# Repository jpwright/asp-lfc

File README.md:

asp-lfc
=======

Schematics and code for my MEng project, a portable light field camera based on angle-sensitive pixel imager.

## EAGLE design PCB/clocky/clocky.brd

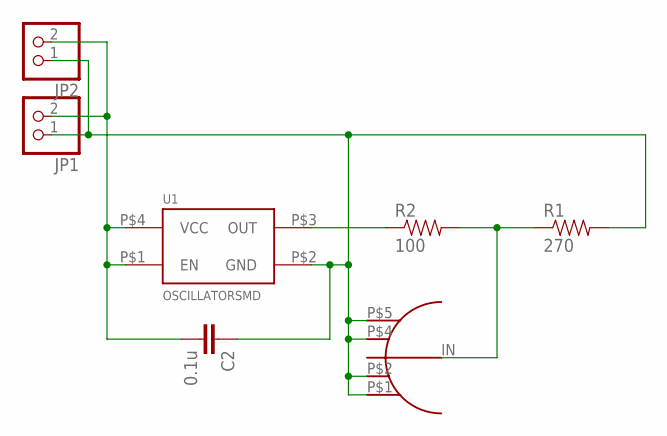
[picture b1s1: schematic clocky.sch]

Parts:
C2: 0.1u; 0603-CAP
JP1: PINHD-1X2/90; 1X02/90
JP2: PINHD-1X2; 1X02
R1: 270; 0603-RES
R2: 100; 0603-RES
U1: OSCILLATORSMD; CRYSTAL-SMD-7X5
U$1: J658; SMA_J658

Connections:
3V3: C2.2, JP1.2, JP2.2, U1.P$1 (EN), U1.P$4 (VCC)
GND: C2.1, JP1.1, JP2.1, R1.2, U1.P$2 (GND), U$1.P$1 (GNDA), U$1.P$2 (GNDB), U$1.P$4 (GNDC), U$1.P$5 (GNDD)
unnamed: R2.1, U1.P$3 (OUT)
unnamed: R1.1, R2.2, U$1.IN

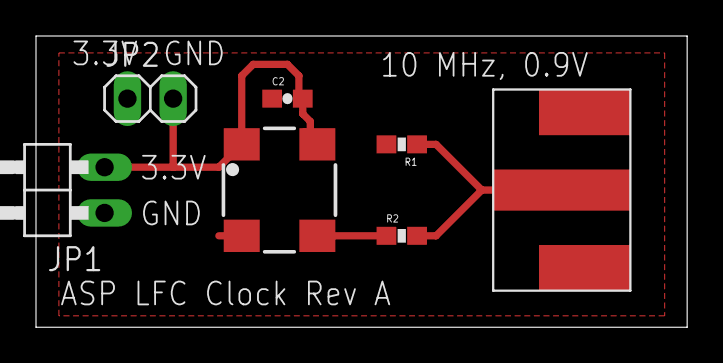
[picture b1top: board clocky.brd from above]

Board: 2 copper layers, 36.2 x 16.2 mm, 7 parts (0 on the bottom side), 4 nets.

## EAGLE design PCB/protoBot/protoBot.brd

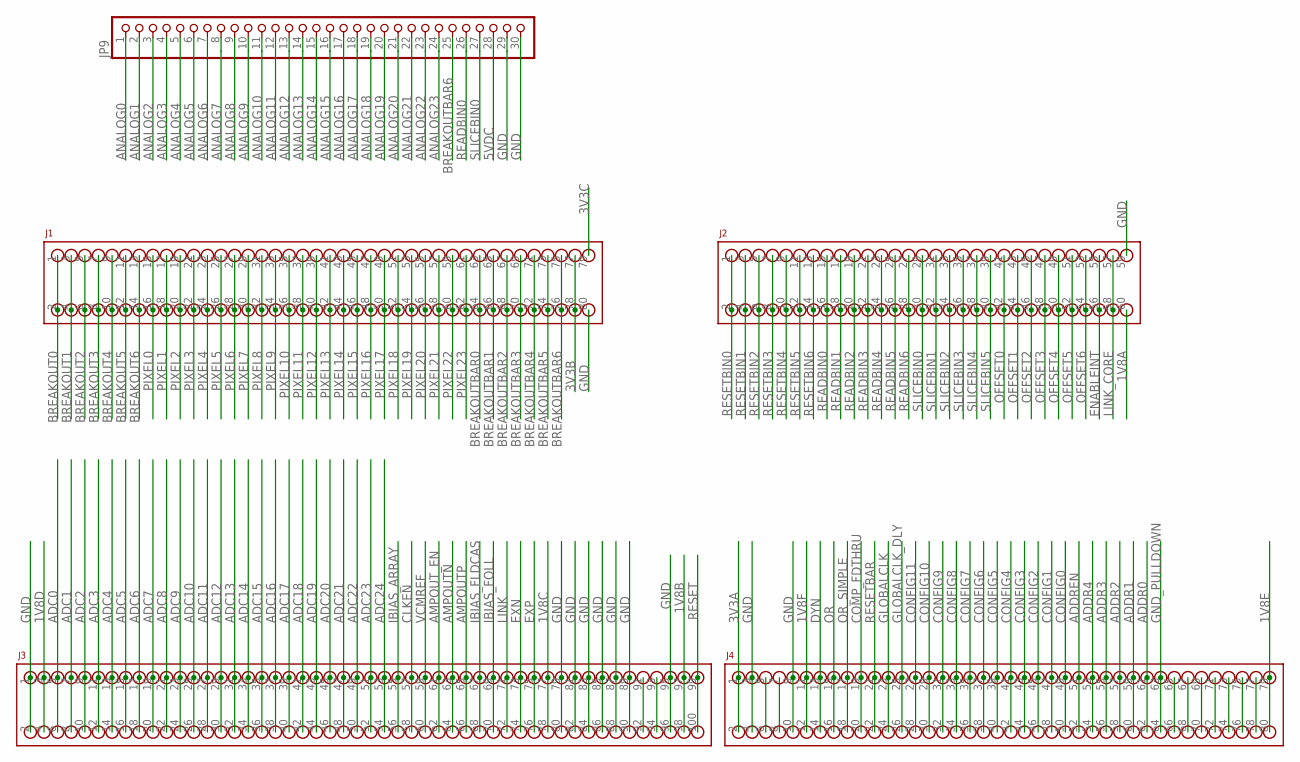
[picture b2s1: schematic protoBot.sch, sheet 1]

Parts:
J1, J4: AMPMODU50-80
J2: AMPMODU50-60
J3: AMPMODU50-100
JP9: PINHD-1X30; 1X30

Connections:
1V8A: J2.60; also elsewhere on the board
1V8B: J3.97, J3.98; also elsewhere on the board
1V8C: J3.77, J3.78; also elsewhere on the board
1V8D: J3.3, J3.4; also elsewhere on the board
1V8E: J4.79, J4.80; also elsewhere on the board
1V8F: J4.11, J4.12; also elsewhere on the board
3V3A: J4.1, J4.2; also elsewhere on the board
3V3B: J1.77, J1.78; also elsewhere on the board
3V3C: J1.79; also elsewhere on the board
5VDC: JP9.28; also elsewhere on the board
ADC0: J3.5, J3.6; also elsewhere on the board
ADC1: J3.7, J3.8; also elsewhere on the board
ADC2: J3.9, J3.10; also elsewhere on the board
ADC3: J3.11, J3.12; also elsewhere on the board
ADC4: J3.13, J3.14; also elsewhere on the board
ADC5: J3.15, J3.16; also elsewhere on the board
ADC6: J3.17, J3.18; also elsewhere on the board
ADC7: J3.19, J3.20; also elsewhere on the board
ADC8: J3.21, J3.22; also elsewhere on the board
ADC9: J3.23, J3.24; also elsewhere on the board
ADC10: J3.25, J3.26; also elsewhere on the board
ADC11: J3.27, J3.28; also elsewhere on the board
ADC12: J3.29, J3.30; also elsewhere on the board
ADC13: J3.31, J3.32; also elsewhere on the board
ADC14: J3.33, J3.34; also elsewhere on the board
ADC15: J3.35, J3.36; also elsewhere on the board
ADC16: J3.37, J3.38; also elsewhere on the board
ADC17: J3.39, J3.40; also elsewhere on the board
ADC18: J3.41, J3.42; also elsewhere on the board
ADC19: J3.43, J3.44; also elsewhere on the board
ADC20: J3.45, J3.46; also elsewhere on the board
ADC21: J3.47, J3.48; also elsewhere on the board
ADC22: J3.49, J3.50; also elsewhere on the board
ADC23: J3.51, J3.52; also elsewhere on the board
ADC24: J3.53, J3.54; also elsewhere on the board
ADDR0: J4.61, J4.62; also elsewhere on the board
ADDR1: J4.59, J4.60; also elsewhere on the board
ADDR2: J4.57, J4.58; also elsewhere on the board
ADDR3: J4.55, J4.56; also elsewhere on the board
ADDR4: J4.53, J4.54; also elsewhere on the board
ADDREN: J4.51, J4.52; also elsewhere on the board
AMPOUTN: J3.63, J3.64; also elsewhere on the board
AMPOUTP: J3.65, J3.66; also elsewhere on the board
AMPOUT_EN: J3.61, J3.62; also elsewhere on the board
ANALOG0: JP9.1; also elsewhere on the board
ANALOG1: JP9.2; also elsewhere on the board
ANALOG2: JP9.3; also elsewhere on the board
ANALOG3: JP9.4; also elsewhere on the board
ANALOG4: JP9.5; also elsewhere on the board
ANALOG5: JP9.6; also elsewhere on the board
ANALOG6: JP9.7; also elsewhere on the board
ANALOG7: JP9.8; also elsewhere on the board
ANALOG8: JP9.9; also elsewhere on the board
ANALOG9: JP9.10; also elsewhere on the board
ANALOG10: JP9.11; also elsewhere on the board
ANALOG11: JP9.12; also elsewhere on the board
ANALOG12: JP9.13; also elsewhere on the board
ANALOG13: JP9.14; also elsewhere on the board
ANALOG14: JP9.15; also elsewhere on the board
ANALOG15: JP9.16; also elsewhere on the board
ANALOG16: JP9.17; also elsewhere on the board
ANALOG17: JP9.18; also elsewhere on the board
ANALOG18: JP9.19; also elsewhere on the board
ANALOG19: JP9.20; also elsewhere on the board
ANALOG20: JP9.21; also elsewhere on the board
ANALOG21: JP9.22; also elsewhere on the board
ANALOG22: JP9.23; also elsewhere on the board
ANALOG23: JP9.24; also elsewhere on the board
BREAKOUT0: J1.1, J1.2; also elsewhere on the board
BREAKOUT1: J1.3, J1.4; also elsewhere on the board
BREAKOUT2: J1.5, J1.6; also elsewhere on the board
BREAKOUT3: J1.7, J1.8; also elsewhere on the board
BREAKOUT4: J1.9, J1.10; also elsewhere on the board
BREAKOUT5: J1.11, J1.12; also elsewhere on the board
BREAKOUT6: J1.13, J1.14; also elsewhere on the board
BREAKOUTBAR0: J1.63, J1.64; also elsewhere on the board
BREAKOUTBAR1: J1.65, J1.66; also elsewhere on the board
BREAKOUTBAR2: J1.67, J1.68; also elsewhere on the board
BREAKOUTBAR3: J1.69, J1.70; also elsewhere on the board
BREAKOUTBAR4: J1.71, J1.72; also elsewhere on the board
BREAKOUTBAR5: J1.73, J1.74; also elsewhere on the board
BREAKOUTBAR6: J1.75, J1.76, JP9.25; also elsewhere on the board
CLKEN: J3.57, J3.58; also elsewhere on the board
COMP_FDTHRU: J4.19, J4.20; also elsewhere on the board
CONFIG0: J4.49, J4.50; also elsewhere on the board
CONFIG1: J4.47, J4.48; also elsewhere on the board
CONFIG2: J4.45, J4.46; also elsewhere on the board
CONFIG3: J4.43, J4.44; also elsewhere on the board
CONFIG4: J4.41, J4.42; also elsewhere on the board
CONFIG5: J4.39, J4.40; also elsewhere on the board
CONFIG6: J4.37, J4.38; also elsewhere on the board
CONFIG7: J4.35, J4.36; also elsewhere on the board
CONFIG8: J4.33, J4.34; also elsewhere on the board
CONFIG9: J4.31, J4.32; also elsewhere on the board
CONFIG10: J4.29, J4.30; also elsewhere on the board
CONFIG11: J4.27, J4.28; also elsewhere on the board
DYN: J4.13, J4.14
ENABLEINT: J2.55, J2.56; also elsewhere on the board
EXN: J3.73, J3.74; also elsewhere on the board
EXP: J3.75, J3.76; also elsewhere on the board
GLOBALCLK: J4.23, J4.24
GLOBALCLK_DLY: J4.25, J4.26
GND: J1.80, J2.59, J3.1, J3.2, J3.79, J3.80, J3.81, J3.82, J3.83, J3.84, J3.85, J3.86, J3.87, J3.88, J3.89, J3.90, J3.95, J3.96, J4.3, J4.4, J4.9, J4.10, JP9.29, JP9.30; also elsewhere on the board
GND_PULLDOWN: J4.63, J4.64; also elsewhere on the board
IBIAS_ARRAY: J3.55, J3.56; also elsewhere on the board
IBIAS_FLDCAS: J3.67, J3.68; also elsewhere on the board
IBIAS_FOLL: J3.69, J3.70; also elsewhere on the board
LINK: J3.71, J3.72; also elsewhere on the board
LINK_CORE: J2.57, J2.58; also elsewhere on the board
unnamed: J4.5, J4.6
unnamed: J4.7, J4.8
unnamed: J4.65, J4.66
unnamed: J4.67, J4.68
unnamed: J4.69, J4.70
unnamed: J4.71, J4.72
unnamed: J4.73, J4.74
unnamed: J4.75, J4.76
unnamed: J4.77, J4.78
unnamed: J3.91, J3.92
unnamed: J3.93, J3.94
OFFSET0: J2.41, J2.42; also elsewhere on the board
OFFSET1: J2.43, J2.44; also elsewhere on the board
OFFSET2: J2.45, J2.46; also elsewhere on the board
OFFSET3: J2.47, J2.48; also elsewhere on the board
OFFSET4: J2.49, J2.50; also elsewhere on the board
OFFSET5: J2.51, J2.52; also elsewhere on the board
OFFSET6: J2.53, J2.54; also elsewhere on the board
OR: J4.15, J4.16; also elsewhere on the board
OR_SIMPLE: J4.17, J4.18; also elsewhere on the board
PIXEL0: J1.15, J1.16; also elsewhere on the board
PIXEL1: J1.17, J1.18; also elsewhere on the board
PIXEL2: J1.19, J1.20; also elsewhere on the board
PIXEL3: J1.21, J1.22; also elsewhere on the board
PIXEL4: J1.23, J1.24; also elsewhere on the board
PIXEL5: J1.25, J1.26; also elsewhere on the board
PIXEL6: J1.27, J1.28; also elsewhere on the board
PIXEL7: J1.29, J1.30; also elsewhere on the board
PIXEL8: J1.31, J1.32; also elsewhere on the board
PIXEL9: J1.33, J1.34; also elsewhere on the board
PIXEL10: J1.35, J1.36; also elsewhere on the board
PIXEL11: J1.37, J1.38; also elsewhere on the board
PIXEL12: J1.39, J1.40; also elsewhere on the board
PIXEL13: J1.41, J1.42; also elsewhere on the board
PIXEL14: J1.43, J1.44; also elsewhere on the board
PIXEL15: J1.45, J1.46; also elsewhere on the board
PIXEL16: J1.47, J1.48; also elsewhere on the board
PIXEL17: J1.49, J1.50; also elsewhere on the board
PIXEL18: J1.51, J1.52; also elsewhere on the board
PIXEL19: J1.53, J1.54; also elsewhere on the board
PIXEL20: J1.55, J1.56; also elsewhere on the board
PIXEL21: J1.57, J1.58; also elsewhere on the board
PIXEL22: J1.59, J1.60; also elsewhere on the board
PIXEL23: J1.61, J1.62; also elsewhere on the board
READBIN0: J2.15, J2.16, JP9.26; also elsewhere on the board
READBIN1: J2.17, J2.18
READBIN2: J2.19, J2.20
READBIN3: J2.21, J2.22
READBIN4: J2.23, J2.24
READBIN5: J2.25, J2.26
READBIN6: J2.27, J2.28; also elsewhere on the board
RESET: J3.99, J3.100; also elsewhere on the board
RESETBAR: J4.21, J4.22
RESETBIN0: J2.1, J2.2
RESETBIN1: J2.3, J2.4
RESETBIN2: J2.5, J2.6
RESETBIN3: J2.7, J2.8
RESETBIN4: J2.9, J2.10
RESETBIN5: J2.11, J2.12
RESETBIN6: J2.13, J2.14
SLICEBIN0: J2.29, J2.30, JP9.27; also elsewhere on the board
SLICEBIN1: J2.31, J2.32; also elsewhere on the board
SLICEBIN2: J2.33, J2.34; also elsewhere on the board
SLICEBIN3: J2.35, J2.36; also elsewhere on the board
SLICEBIN4: J2.37, J2.38; also elsewhere on the board
SLICEBIN5: J2.39, J2.40; also elsewhere on the board
VCMREF: J3.59, J3.60; also elsewhere on the board

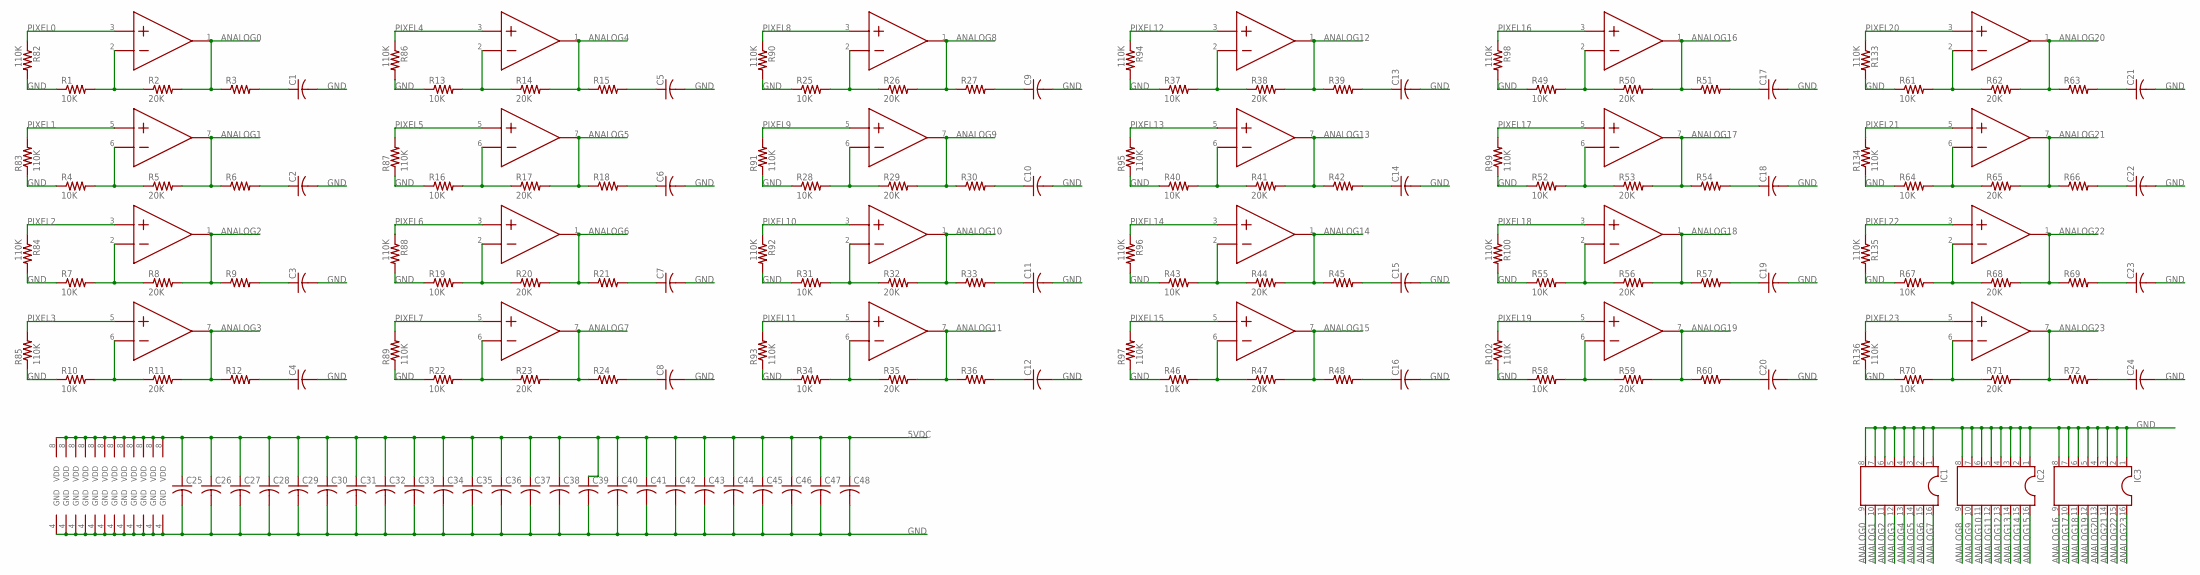
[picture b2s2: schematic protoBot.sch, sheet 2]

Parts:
C1, C2, C3, C4, C5, C6, C7, C8, C9, C10, C11, C12, C13, C14, C15, C16, C17, C18, C19, C20, C21, C22, C23, C24, C25, C26, C27, C28, C29, C30, C31, C32, C33, C34, C35, C36, C37, C38, C39, C40, C41, C42, C43, C44, C45, C46, C47, C48: C-USC0603; C0603
IC1, IC2, IC3: DIL16S; SOCKET-16
R1, R4, R7, R10, R13, R16, R19, R22, R25, R28, R31, R34, R37, R40, R43, R46, R49, R52, R55, R58, R61, R64, R67, R70: 10K; R0603
R2, R5, R8, R11, R14, R17, R20, R23, R26, R29, R32, R35, R38, R41, R44, R47, R50, R53, R56, R59, R62, R65, R68, R71: 20K; R0603
R3, R6, R9, R12, R15, R18, R21, R24, R27, R30, R33, R36, R39, R42, R45, R48, R51, R54, R57, R60, R63, R66, R69, R72: R-US_R0603; R0603
R82, R83, R84, R85, R86, R87, R88, R89, R90, R91, R92, R93, R94, R95, R96, R97, R98, R99, R100, R102, R133, R134, R135, R136: 110K; R0603
U$1, U$2, U$3, U$4, U$5, U$6, U$7, U$8, U$9, U$10, U$11, U$12: AD823; SOIC-8

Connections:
5VDC: C25.1, C26.1, C27.1, C28.1, C29.1, C30.1, C31.1, C32.1, C33.1, C34.1, C35.1, C36.1, C37.1, C38.1, C39.1, C40.1, C41.1, C42.1, C43.1, C44.1, C45.1, C46.1, C47.1, C48.1, U$1.8 (VDD), U$2.8 (VDD), U$3.8 (VDD), U$4.8 (VDD), U$5.8 (VDD), U$6.8 (VDD), U$7.8 (VDD), U$8.8 (VDD), U$9.8 (VDD), U$10.8 (VDD), U$11.8 (VDD), U$12.8 (VDD); also elsewhere on the board
ANALOG0: IC1.9, R2.2, R3.1, U$1.1 (OUT); also elsewhere on the board
ANALOG1: IC1.10, R5.2, R6.1, U$1.7 (OUT); also elsewhere on the board
ANALOG2: IC1.11, R8.2, R9.1, U$2.1 (OUT); also elsewhere on the board
ANALOG3: IC1.12, R11.2, R12.1, U$2.7 (OUT); also elsewhere on the board
ANALOG4: IC1.13, R14.2, R15.1, U$3.1 (OUT); also elsewhere on the board
ANALOG5: IC1.14, R17.2, R18.1, U$3.7 (OUT); also elsewhere on the board
ANALOG6: IC1.15, R20.2, R21.1, U$4.1 (OUT); also elsewhere on the board
ANALOG7: IC1.16, R23.2, R24.1, U$4.7 (OUT); also elsewhere on the board
ANALOG8: IC2.9, R26.2, R27.1, U$5.1 (OUT); also elsewhere on the board
ANALOG9: IC2.10, R29.2, R30.1, U$5.7 (OUT); also elsewhere on the board
ANALOG10: IC2.11, R32.2, R33.1, U$6.1 (OUT); also elsewhere on the board
ANALOG11: IC2.12, R35.2, R36.1, U$6.7 (OUT); also elsewhere on the board
ANALOG12: IC2.13, R38.2, R39.1, U$7.1 (OUT); also elsewhere on the board
ANALOG13: IC2.14, R41.2, R42.1, U$7.7 (OUT); also elsewhere on the board
ANALOG14: IC2.15, R44.2, R45.1, U$8.1 (OUT); also elsewhere on the board
ANALOG15: IC2.16, R47.2, R48.1, U$8.7 (OUT); also elsewhere on the board
ANALOG16: IC3.9, R50.2, R51.1, U$9.1 (OUT); also elsewhere on the board
ANALOG17: IC3.10, R53.2, R54.1, U$9.7 (OUT); also elsewhere on the board
ANALOG18: IC3.11, R56.2, R57.1, U$10.1 (OUT); also elsewhere on the board
ANALOG19: IC3.12, R59.2, R60.1, U$10.7 (OUT); also elsewhere on the board
ANALOG20: IC3.13, R62.2, R63.1, U$11.1 (OUT); also elsewhere on the board
ANALOG21: IC3.14, R65.2, R66.1, U$11.7 (OUT); also elsewhere on the board
ANALOG22: IC3.15, R68.2, R69.1, U$12.1 (OUT); also elsewhere on the board
ANALOG23: IC3.16, R71.2, R72.1, U$12.7 (OUT); also elsewhere on the board
GND: C1.2, C2.2, C3.2, C4.2, C5.2, C6.2, C7.2, C8.2, C9.2, C10.2, C11.2, C12.2, C13.2, C14.2, C15.2, C16.2, C17.2, C18.2, C19.2, C20.2, C21.2, C22.2, C23.2, C24.2, C25.2, C26.2, C27.2, C28.2, C29.2, C30.2, C31.2, C32.2, C33.2, C34.2, C35.2, C36.2, C37.2, C38.2, C39.2, C40.2, C41.2, C42.2, C43.2, C44.2, C45.2, C46.2, C47.2, C48.2, IC1.1, IC1.2, IC1.3, IC1.4, IC1.5, IC1.6, IC1.7, IC1.8, IC2.1, IC2.2, IC2.3, IC2.4, IC2.5, IC2.6, IC2.7, IC2.8, IC3.1, IC3.2, IC3.3, IC3.4, IC3.5, IC3.6, IC3.7, IC3.8, R1.1, R4.1, R7.1, R10.1, R13.1, R16.1, R19.1, R22.1, R25.1, R28.1, R31.1, R34.1, R37.1, R40.1, R43.1, R46.1, R49.1, R52.1, R55.1, R58.1, R61.1, R64.1, R67.1, R70.1, R82.2, R83.1, R84.2, R85.1, R86.2, R87.1, R88.2, R89.1, R90.2, R91.1, R92.2, R93.1, R94.2, R95.1, R96.2, R97.1, R98.2, R99.1, R100.2, R102.1, R133.2, R134.1, R135.2, R136.1, U$1.4 (GND), U$2.4 (GND), U$3.4 (GND), U$4.4 (GND), U$5.4 (GND), U$6.4 (GND), U$7.4 (GND), U$8.4 (GND), U$9.4 (GND), U$10.4 (GND), U$11.4 (GND), U$12.4 (GND); also elsewhere on the board
unnamed: R1.2, R2.1, U$1.2 (IN-)
unnamed: C1.1, R3.2
unnamed: R13.2, R14.1, U$3.2 (IN-)
unnamed: C5.1, R15.2
unnamed: R4.2, R5.1, U$1.6 (IN-)
unnamed: C2.1, R6.2
unnamed: R16.2, R17.1, U$3.6 (IN-)
unnamed: R7.2, R8.1, U$2.2 (IN-)
unnamed: C3.1, R9.2
unnamed: C6.1, R18.2
unnamed: R19.2, R20.1, U$4.2 (IN-)
unnamed: R10.2, R11.1, U$2.6 (IN-)
unnamed: C4.1, R12.2
unnamed: C7.1, R21.2
unnamed: R22.2, R23.1, U$4.6 (IN-)
unnamed: C8.1, R24.2
unnamed: R25.2, R26.1, U$5.2 (IN-)
unnamed: C9.1, R27.2
unnamed: R28.2, R29.1, U$5.6 (IN-)
unnamed: C10.1, R30.2
unnamed: R31.2, R32.1, U$6.2 (IN-)
unnamed: C11.1, R33.2
unnamed: R34.2, R35.1, U$6.6 (IN-)
unnamed: C12.1, R36.2
unnamed: R37.2, R38.1, U$7.2 (IN-)
unnamed: C13.1, R39.2
unnamed: R40.2, R41.1, U$7.6 (IN-)
unnamed: C14.1, R42.2
unnamed: R43.2, R44.1, U$8.2 (IN-)
unnamed: C15.1, R45.2
unnamed: R46.2, R47.1, U$8.6 (IN-)
unnamed: C16.1, R48.2
unnamed: R49.2, R50.1, U$9.2 (IN-)
unnamed: C17.1, R51.2
unnamed: R52.2, R53.1, U$9.6 (IN-)
unnamed: C18.1, R54.2
unnamed: R55.2, R56.1, U$10.2 (IN-)
unnamed: C19.1, R57.2
unnamed: R58.2, R59.1, U$10.6 (IN-)
unnamed: C20.1, R60.2
unnamed: R61.2, R62.1, U$11.2 (IN-)
unnamed: C21.1, R63.2
unnamed: R64.2, R65.1, U$11.6 (IN-)
unnamed: C22.1, R66.2
unnamed: R67.2, R68.1, U$12.2 (IN-)
unnamed: C23.1, R69.2
unnamed: R70.2, R71.1, U$12.6 (IN-)
unnamed: C24.1, R72.2
PIXEL0: R82.1, U$1.3 (IN+); also elsewhere on the board
PIXEL1: R83.2, U$1.5 (IN+); also elsewhere on the board
PIXEL2: R84.1, U$2.3 (IN+); also elsewhere on the board
PIXEL3: R85.2, U$2.5 (IN+); also elsewhere on the board
PIXEL4: R86.1, U$3.3 (IN+); also elsewhere on the board
PIXEL5: R87.2, U$3.5 (IN+); also elsewhere on the board
PIXEL6: R88.1, U$4.3 (IN+); also elsewhere on the board
PIXEL7: R89.2, U$4.5 (IN+); also elsewhere on the board
PIXEL8: R90.1, U$5.3 (IN+); also elsewhere on the board
PIXEL9: R91.2, U$5.5 (IN+); also elsewhere on the board
PIXEL10: R92.1, U$6.3 (IN+); also elsewhere on the board
PIXEL11: R93.2, U$6.5 (IN+); also elsewhere on the board
PIXEL12: R94.1, U$7.3 (IN+); also elsewhere on the board
PIXEL13: R95.2, U$7.5 (IN+); also elsewhere on the board
PIXEL14: R96.1, U$8.3 (IN+); also elsewhere on the board
PIXEL15: R97.2, U$8.5 (IN+); also elsewhere on the board
PIXEL16: R98.1, U$9.3 (IN+); also elsewhere on the board
PIXEL17: R99.2, U$9.5 (IN+); also elsewhere on the board
PIXEL18: R100.1, U$10.3 (IN+); also elsewhere on the board
PIXEL19: R102.2, U$10.5 (IN+); also elsewhere on the board
PIXEL20: R133.1, U$11.3 (IN+); also elsewhere on the board
PIXEL21: R134.2, U$11.5 (IN+); also elsewhere on the board
PIXEL22: R135.1, U$12.3 (IN+); also elsewhere on the board
PIXEL23: R136.2, U$12.5 (IN+); also elsewhere on the board

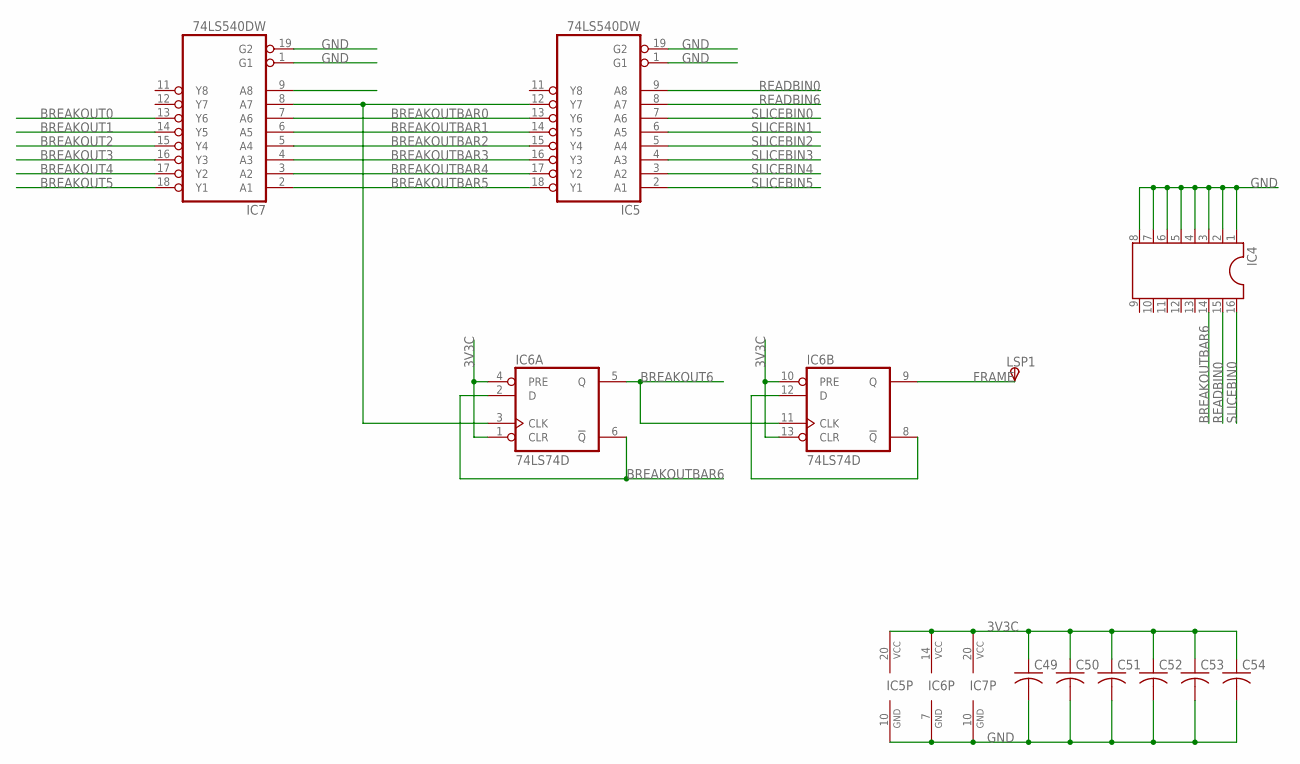
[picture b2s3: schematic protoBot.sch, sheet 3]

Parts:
C49, C50, C51, C52, C53, C54: C-USC0603; C0603
IC4: DIL16S; SOCKET-16
IC5, IC7: 74LS540DW; SO20W
IC6: 74LS74D; SO14
LSP1: TPSPAD1-13; P1-13

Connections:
3V3C: C49.1, C50.1, C51.1, C52.1, C53.1, C54.1, IC5.20 (VCC), IC6.1 (CLR), IC6.4 (PRE), IC6.10 (PRE), IC6.13 (CLR), IC6.14 (VCC), IC7.20 (VCC); also elsewhere on the board
BREAKOUT0: IC7.13 (Y6); also elsewhere on the board
BREAKOUT1: IC7.14 (Y5); also elsewhere on the board
BREAKOUT2: IC7.15 (Y4); also elsewhere on the board
BREAKOUT3: IC7.16 (Y3); also elsewhere on the board
BREAKOUT4: IC7.17 (Y2); also elsewhere on the board
BREAKOUT5: IC7.18 (Y1); also elsewhere on the board
BREAKOUT6: IC6.5 (Q), IC6.11 (CLK); also elsewhere on the board
BREAKOUTBAR0: IC5.13 (Y6), IC7.7 (A6); also elsewhere on the board
BREAKOUTBAR1: IC5.14 (Y5), IC7.6 (A5); also elsewhere on the board
BREAKOUTBAR2: IC5.15 (Y4), IC7.5 (A4); also elsewhere on the board
BREAKOUTBAR3: IC5.16 (Y3), IC7.4 (A3); also elsewhere on the board
BREAKOUTBAR4: IC5.17 (Y2), IC7.3 (A2); also elsewhere on the board
BREAKOUTBAR5: IC5.18 (Y1), IC7.2 (A1); also elsewhere on the board
BREAKOUTBAR6: IC4.14, IC6.2 (D), IC6.6 (!Q); also elsewhere on the board
FRAME: IC6.9 (Q), LSP1.1
GND: C49.2, C50.2, C51.2, C52.2, C53.2, C54.2, IC4.1, IC4.2, IC4.3, IC4.4, IC4.5, IC4.6, IC4.7, IC4.8, IC5.1 (G1), IC5.10 (GND), IC5.19 (G2), IC6.7 (GND), IC7.1 (G1), IC7.9 (A8), IC7.10 (GND), IC7.19 (G2); also elsewhere on the board
unnamed: IC5.12 (Y7), IC6.3 (CLK), IC7.8 (A7)
unnamed: IC6.8 (!Q), IC6.12 (D)
READBIN0: IC4.15, IC5.9 (A8); also elsewhere on the board
READBIN6: IC5.8 (A7); also elsewhere on the board
SLICEBIN0: IC4.16, IC5.7 (A6); also elsewhere on the board
SLICEBIN1: IC5.6 (A5); also elsewhere on the board
SLICEBIN2: IC5.5 (A4); also elsewhere on the board
SLICEBIN3: IC5.4 (A3); also elsewhere on the board
SLICEBIN4: IC5.3 (A2); also elsewhere on the board
SLICEBIN5: IC5.2 (A1); also elsewhere on the board

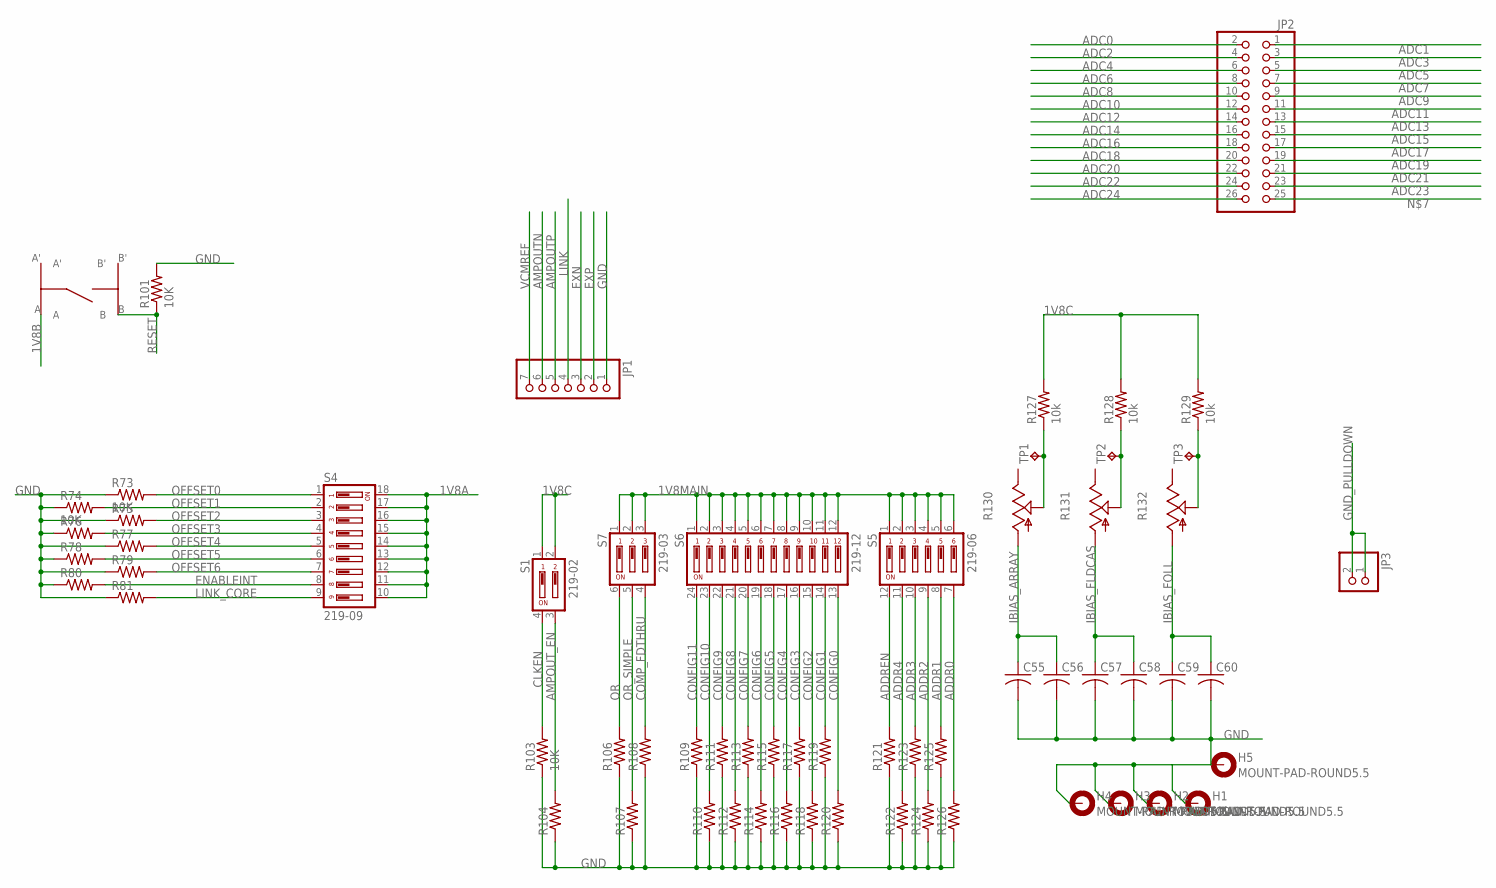
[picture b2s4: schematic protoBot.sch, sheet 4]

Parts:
C55, C57, C59: C-USC1210; C1210
C56, C58, C60: C-USC0603; C0603
H1, H2, H3, H4, H5: MOUNT-PAD-ROUND5.5; 5,5-PAD
JP1: PINHD-1X7; 1X07
JP2: PINHD-2X13; 2X13
JP3: PINHD-1X2; 1X02
R73, R74, R101, R103: 10K; R0603
R75, R76, R77, R78, R79, R80, R81, R104, R106, R107, R108, R109, R110, R111, R112, R113, R114, R115, R116, R117, R118, R119, R120, R121, R122, R123, R124, R125, R126: R-US_R0603; R0603
R127, R128, R129: 10k; R0603
R130, R131, R132: TRIM_US-B64Y; B64Y
S1: 219-02; CTS-219-02
S2: EVQPA
S4: 219-09; CTS-219-09
S5: 219-06; CTS-219-06
S6: 219-12; CTS-219-12
S7: 219-03; CTS-219-03
TP1, TP2, TP3: TPTP20R; TP20R

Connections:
1V8A: S4.10, S4.11, S4.12, S4.13, S4.14, S4.15, S4.16, S4.17, S4.18; also elsewhere on the board
1V8B: S2.A; also elsewhere on the board
1V8C: R127.2, R128.2, R129.2, S1.1, S1.2; also elsewhere on the board
1V8MAIN: S5.1, S5.2, S5.3, S5.4, S5.5, S5.6, S6.1, S6.2, S6.3, S6.4, S6.5, S6.6, S6.7, S6.8, S6.9, S6.10, S6.11, S6.12, S7.1, S7.2, S7.3; also elsewhere on the board
ADC0: JP2.2; also elsewhere on the board
ADC1: JP2.1; also elsewhere on the board
ADC2: JP2.4; also elsewhere on the board
ADC3: JP2.3; also elsewhere on the board
ADC4: JP2.6; also elsewhere on the board
ADC5: JP2.5; also elsewhere on the board
ADC6: JP2.8; also elsewhere on the board
ADC7: JP2.7; also elsewhere on the board
ADC8: JP2.10; also elsewhere on the board
ADC9: JP2.9; also elsewhere on the board
ADC10: JP2.12; also elsewhere on the board
ADC11: JP2.11; also elsewhere on the board
ADC12: JP2.14; also elsewhere on the board
ADC13: JP2.13; also elsewhere on the board
ADC14: JP2.16; also elsewhere on the board
ADC15: JP2.15; also elsewhere on the board
ADC16: JP2.18; also elsewhere on the board
ADC17: JP2.17; also elsewhere on the board
ADC18: JP2.20; also elsewhere on the board
ADC19: JP2.19; also elsewhere on the board
ADC20: JP2.22; also elsewhere on the board
ADC21: JP2.21; also elsewhere on the board
ADC22: JP2.24; also elsewhere on the board
ADC23: JP2.23; also elsewhere on the board
ADC24: JP2.26; also elsewhere on the board
ADDR0: R126.2, S5.7; also elsewhere on the board
ADDR1: R125.2, S5.8; also elsewhere on the board
ADDR2: R124.2, S5.9; also elsewhere on the board
ADDR3: R123.2, S5.10; also elsewhere on the board
ADDR4: R122.2, S5.11; also elsewhere on the board
ADDREN: R121.2, S5.12; also elsewhere on the board
AMPOUTN: JP1.6; also elsewhere on the board
AMPOUTP: JP1.5; also elsewhere on the board
AMPOUT_EN: R104.2, S1.3; also elsewhere on the board
CLKEN: R103.2, S1.4; also elsewhere on the board
COMP_FDTHRU: R108.2, S7.4; also elsewhere on the board
CONFIG0: R120.2, S6.13; also elsewhere on the board
CONFIG1: R119.2, S6.14; also elsewhere on the board
CONFIG2: R118.2, S6.15; also elsewhere on the board
CONFIG3: R117.2, S6.16; also elsewhere on the board
CONFIG4: R116.2, S6.17; also elsewhere on the board
CONFIG5: R115.2, S6.18; also elsewhere on the board
CONFIG6: R114.2, S6.19; also elsewhere on the board
CONFIG7: R113.2, S6.20; also elsewhere on the board
CONFIG8: R112.2, S6.21; also elsewhere on the board
CONFIG9: R111.2, S6.22; also elsewhere on the board
CONFIG10: R110.2, S6.23; also elsewhere on the board
CONFIG11: R109.2, S6.24; also elsewhere on the board
ENABLEINT: R80.2, S4.8; also elsewhere on the board
EXN: JP1.3; also elsewhere on the board
EXP: JP1.2; also elsewhere on the board
GND: C55.2, C56.2, C57.2, C58.2, C59.2, C60.2, H1.B5,5, H2.B5,5, H3.B5,5, H4.B5,5, H5.B5,5, JP1.1, R73.1, R74.1, R75.1, R76.1, R77.1, R78.1, R79.1, R80.1, R81.1, R101.2, R103.1, R104.1, R106.1, R107.1, R108.1, R109.1, R110.1, R111.1, R112.1, R113.1, R114.1, R115.1, R116.1, R117.1, R118.1, R119.1, R120.1, R121.1, R122.1, R123.1, R124.1, R125.1, R126.1; also elsewhere on the board
GND_PULLDOWN: JP3.1, JP3.2; also elsewhere on the board
IBIAS_ARRAY: C55.1, C56.1, R130.A; also elsewhere on the board
IBIAS_FLDCAS: C57.1, C58.1, R131.A; also elsewhere on the board
IBIAS_FOLL: C59.1, C60.1, R132.A; also elsewhere on the board
LINK: JP1.4; also elsewhere on the board
LINK_CORE: R81.2, S4.9; also elsewhere on the board
unnamed: R127.1, R130.S, TP1.TP
unnamed: R128.1, R131.S, TP2.TP
unnamed: R129.1, R132.S, TP3.TP
OFFSET0: R73.2, S4.1; also elsewhere on the board
OFFSET1: R74.2, S4.2; also elsewhere on the board
OFFSET2: R75.2, S4.3; also elsewhere on the board
OFFSET3: R76.2, S4.4; also elsewhere on the board
OFFSET4: R77.2, S4.5; also elsewhere on the board
OFFSET5: R78.2, S4.6; also elsewhere on the board
OFFSET6: R79.2, S4.7; also elsewhere on the board
OR: R106.2, S7.6; also elsewhere on the board
OR_SIMPLE: R107.2, S7.5; also elsewhere on the board
RESET: R101.1, S2.B; also elsewhere on the board
VCMREF: JP1.7; also elsewhere on the board

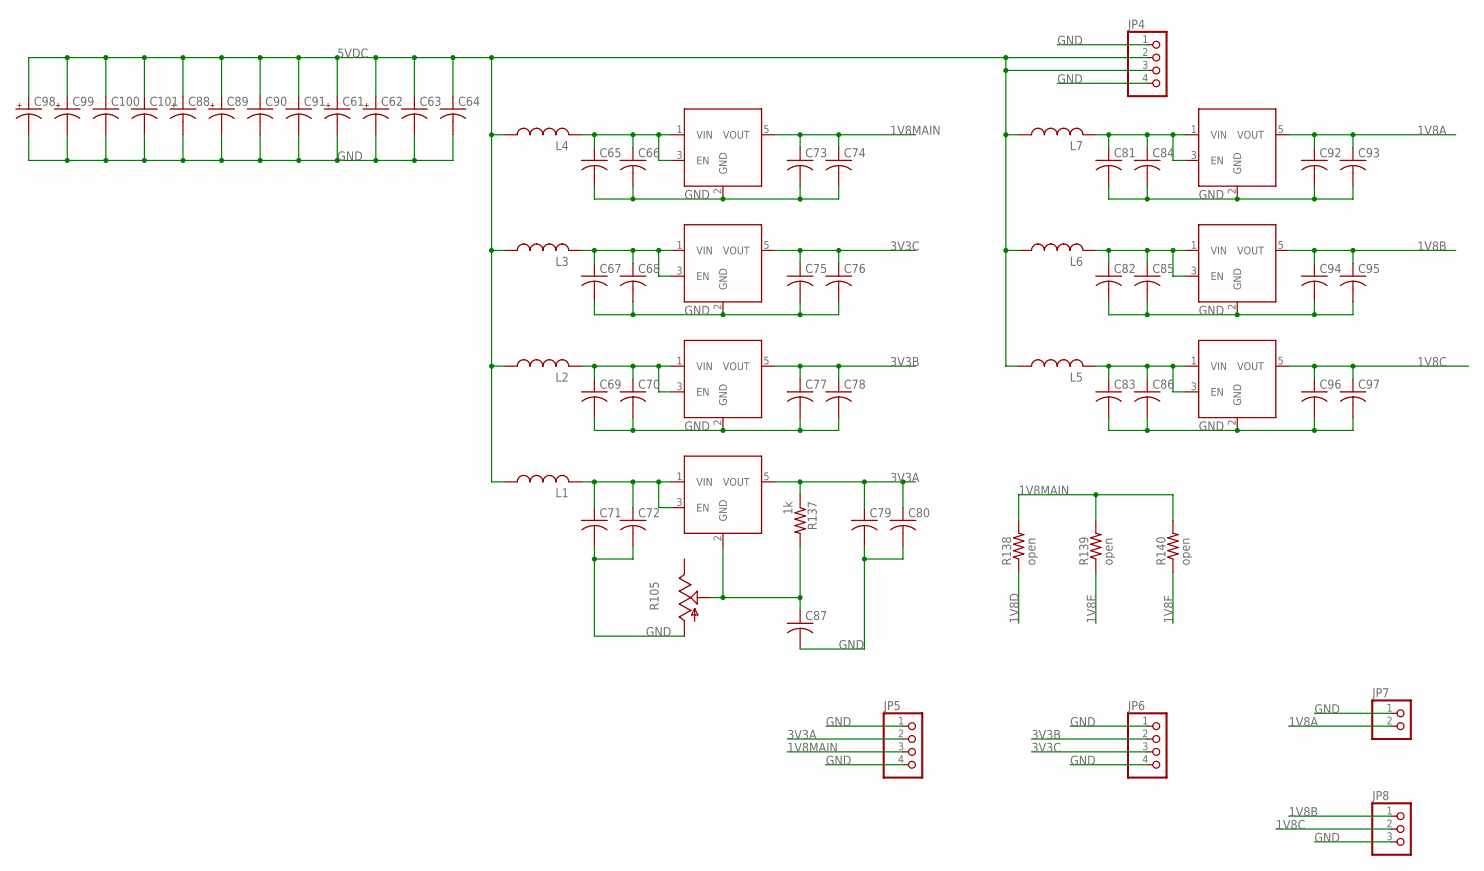
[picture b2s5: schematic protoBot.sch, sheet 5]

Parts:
C61, C62, C88, C89, C98, C99: CPOL-USE/7260-38R; E/7260-38R
C63, C64, C66, C68, C70, C72, C73, C75, C77, C79, C84, C85, C86, C90, C91, C92, C94, C96, C100, C101: C-USC1210; C1210
C65, C67, C69, C71, C74, C76, C78, C80, C81, C82, C83, C87, C93, C95, C97: C-USC0603; C0603
JP4, JP5, JP6: PINHD-1X4; 1X04
JP7: PINHD-1X2; 1X02
JP8: PINHD-1X3; 1X03
L1, L2, L3, L4, L5, L6, L7: L-USL1812; L1812
R105: TRIM_US-B64Y; B64Y
R137: 1k; R0603
R138, R139, R140: open; R1206
U$13, U$14, U$15, U$28, U$29, U$30, U$31: ADP151; TSOT23-5

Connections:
1V8A: C92.1, C93.1, JP7.2, U$13.5 (VOUT); also elsewhere on the board
1V8B: C94.1, C95.1, JP8.1, U$14.5 (VOUT); also elsewhere on the board
1V8C: C96.1, C97.1, JP8.2, U$15.5 (VOUT); also elsewhere on the board
1V8D: R138.1; also elsewhere on the board
1V8E: R139.1; also elsewhere on the board
1V8F: R140.1; also elsewhere on the board
1V8MAIN: C73.1, C74.1, JP5.3, R138.2, R139.2, R140.2, U$28.5 (VOUT); also elsewhere on the board
3V3A: C79.1, C80.1, JP5.2, R137.1, U$31.5 (VOUT); also elsewhere on the board
3V3B: C77.1, C78.1, JP6.2, U$30.5 (VOUT); also elsewhere on the board
3V3C: C75.1, C76.1, JP6.3, U$29.5 (VOUT); also elsewhere on the board
5VDC: C61.+, C62.+, C63.1, C64.1, C88.+, C89.+, C90.1, C91.1, C98.+, C99.+, C100.1, C101.1, JP4.2, JP4.3, L1.1, L2.1, L3.1, L4.1, L5.1, L6.1, L7.1; also elsewhere on the board
GND: C61.-, C62.-, C63.2, C64.2, C65.2, C66.2, C67.2, C68.2, C69.2, C70.2, C71.2, C72.2, C73.2, C74.2, C75.2, C76.2, C77.2, C78.2, C79.2, C80.2, C81.2, C82.2, C83.2, C84.2, C85.2, C86.2, C87.2, C88.-, C89.-, C90.2, C91.2, C92.2, C93.2, C94.2, C95.2, C96.2, C97.2, C98.-, C99.-, C100.2, C101.2, JP4.1, JP4.4, JP5.1, JP5.4, JP6.1, JP6.4, JP7.1, JP8.3, R105.A, U$13.2 (GND), U$14.2 (GND), U$15.2 (GND), U$28.2 (GND), U$29.2 (GND), U$30.2 (GND); also elsewhere on the board
unnamed: C67.1, C68.1, L3.2, U$29.1 (VIN), U$29.3 (EN)
unnamed: C65.1, C66.1, L4.2, U$28.1 (VIN), U$28.3 (EN)
unnamed: C69.1, C70.1, L2.2, U$30.1 (VIN), U$30.3 (EN)
unnamed: C71.1, C72.1, L1.2, U$31.1 (VIN), U$31.3 (EN)
unnamed: C81.1, C84.1, L7.2, U$13.1 (VIN), U$13.3 (EN)
unnamed: C82.1, C85.1, L6.2, U$14.1 (VIN), U$14.3 (EN)
unnamed: C83.1, C86.1, L5.2, U$15.1 (VIN), U$15.3 (EN)
unnamed: C87.1, R105.S, R137.2, U$31.2 (GND)

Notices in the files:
parts and their libraries:
SparkFun-FreqCtrl: Licensing: CC v3.0 Share-Alike You are welcome to use this library for commercial purposes.
